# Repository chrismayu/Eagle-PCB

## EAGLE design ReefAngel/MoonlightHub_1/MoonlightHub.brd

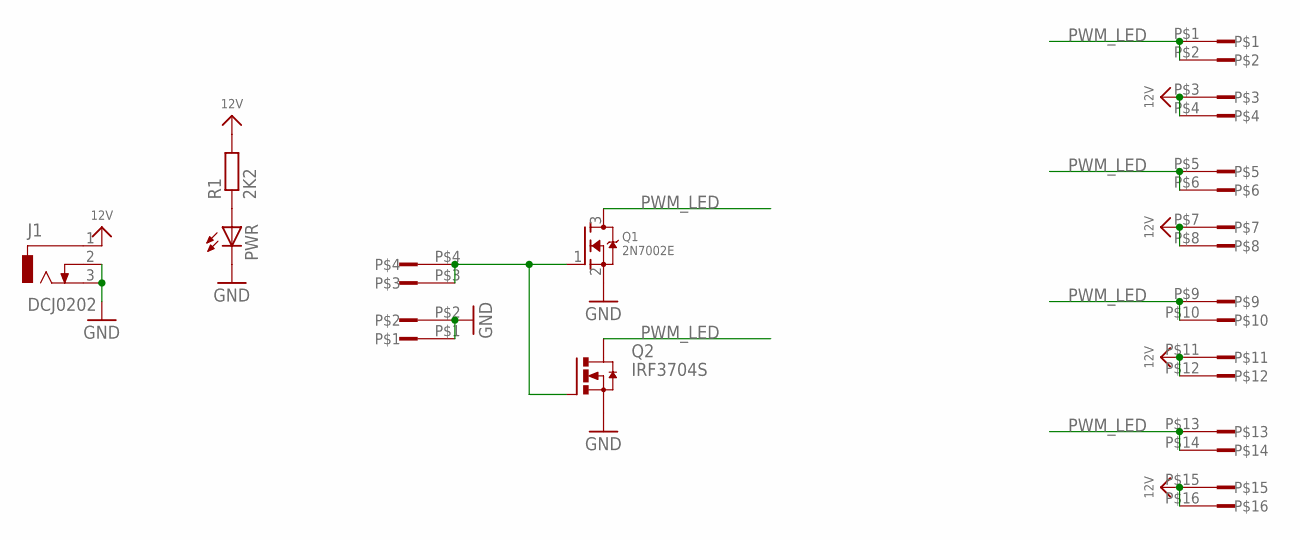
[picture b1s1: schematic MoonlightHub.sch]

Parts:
CON1: CONN2
CON2: CONN8
J1: DCJ0202
PWR: LED3MM
Q1: 2N7002E; SOT23-W
Q2: IRF3704S; D2PACK
R1: 2K2; R0805W

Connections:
12V: CON2.P$3, CON2.P$4, CON2.P$7, CON2.P$8, CON2.P$11, CON2.P$12, CON2.P$15, CON2.P$16, J1.1, R1.2
GND: CON1.P$1, CON1.P$2, J1.2, J1.3, PWR.K (C), Q1.2 (S), Q2.3 (S)
unnamed: CON1.P$3, CON1.P$4, Q1.1 (G), Q2.1 (G)
unnamed: PWR.A, R1.1
PWM_LED: CON2.P$1, CON2.P$2, CON2.P$5, CON2.P$6, CON2.P$9, CON2.P$10, CON2.P$13, CON2.P$14, Q1.3 (D), Q2.2 (D)

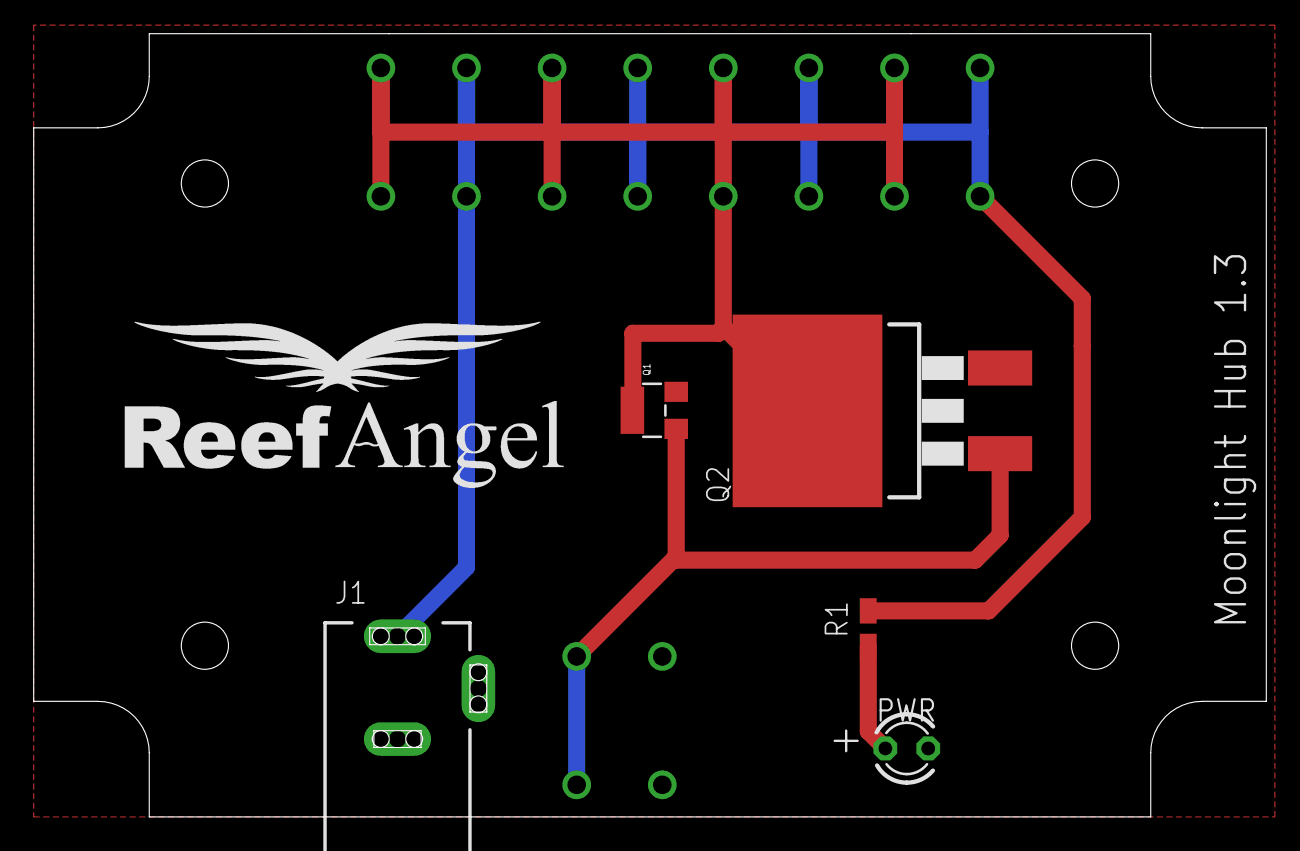
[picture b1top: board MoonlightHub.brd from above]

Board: 2 copper layers, 73.2 x 46.5 mm, 7 parts (0 on the bottom side), 5 nets.

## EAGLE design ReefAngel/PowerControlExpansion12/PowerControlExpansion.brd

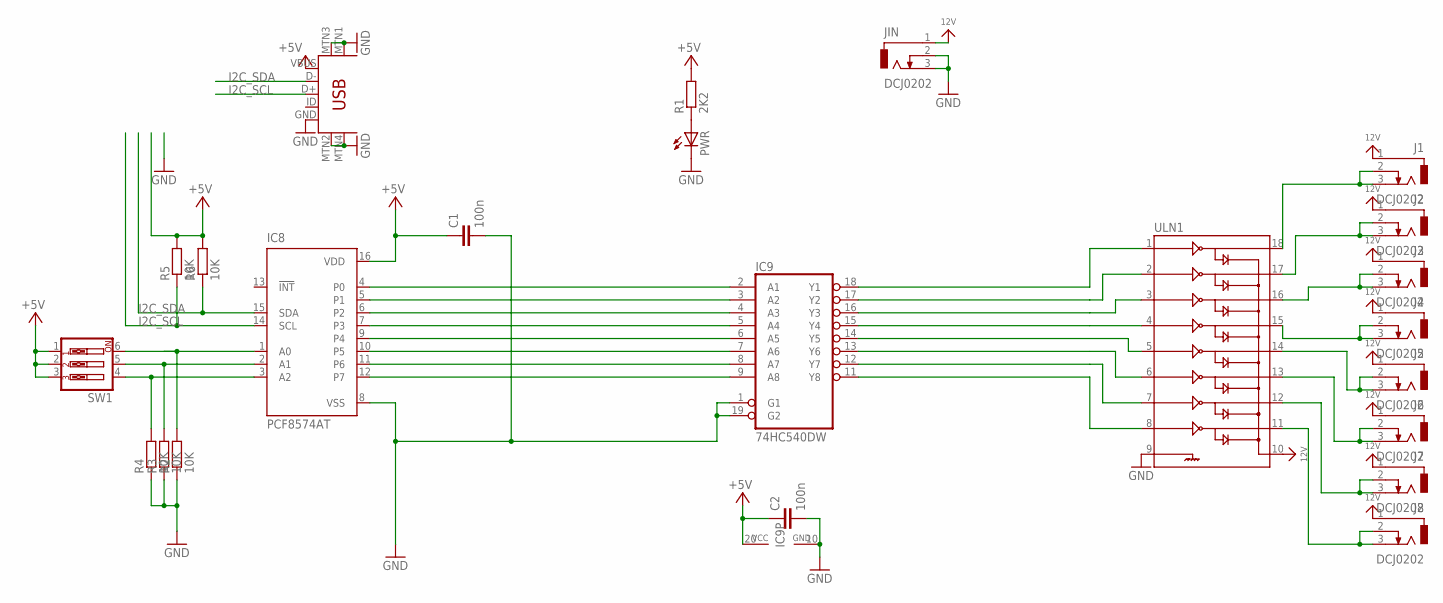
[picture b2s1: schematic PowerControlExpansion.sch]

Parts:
C1, C2: 100n; C0805K
IC8: PCF8574AT; SO16W
IC9: 74HC540DW; SO20W
J1, J2, J3, J4, J5, J6, J7, J8: DCJ0202
JIN: DCJ0202
PWR: LED3MM
R1: 2K2; R0805W
R2, R3, R4, R5, R6: 10K; R0805W
SW1: SW_DIP-3; EDG-03
U1: USB-MINIB-5PIN; USB-MINIB
ULN1: ULN2803SOICW; SO18L

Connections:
12V: J1.1, J2.1, J3.1, J4.1, J5.1, J6.1, J7.1, J8.1, JIN.1, ULN1.10
+5V: C1.1, C2.1, IC8.16 (VDD), IC9.20 (VCC), R1.2, R5.2, R6.2, SW1.1, SW1.2, SW1.3, U1.VBUS
GND: C1.2, C2.2, IC8.8 (VSS), IC9.1 (G1), IC9.10 (GND), IC9.19 (G2), JIN.2, JIN.3, PWR.K (C), R2.1, R3.1, R4.1, U1.GND, U1.MTN1 (MTN2), U1.MTN2 (MTN3), U1.MTN3 (MTN1), U1.MTN4, ULN1.9
I2C_SCL: IC8.14 (SCL), R5.1, U1.D+
I2C_SDA: IC8.15 (SDA), R6.1, U1.D-
unnamed: J1.2, J1.3, ULN1.18
unnamed: J2.2, J2.3, ULN1.17
unnamed: J3.2, J3.3, ULN1.16
unnamed: PWR.A, R1.1
unnamed: J4.2, J4.3, ULN1.15
unnamed: IC9.18 (Y1), ULN1.1
unnamed: J5.2, J5.3, ULN1.14
unnamed: J6.2, J6.3, ULN1.13
unnamed: IC8.2 (A1), R3.2, SW1.5
unnamed: IC8.3 (A2), R4.2, SW1.4
unnamed: IC8.1 (A0), R2.2, SW1.6
unnamed: IC9.17 (Y2), ULN1.2
unnamed: J7.2, J7.3, ULN1.12
unnamed: IC9.16 (Y3), ULN1.3
unnamed: J8.2, J8.3, ULN1.11
unnamed: IC9.15 (Y4), ULN1.4
unnamed: IC9.14 (Y5), ULN1.5
unnamed: IC9.13 (Y6), ULN1.6
unnamed: IC9.12 (Y7), ULN1.7
unnamed: IC9.11 (Y8), ULN1.8
unnamed: IC8.4 (P0), IC9.2 (A1)
unnamed: IC8.5 (P1), IC9.3 (A2)
unnamed: IC8.6 (P2), IC9.4 (A3)
unnamed: IC8.7 (P3), IC9.5 (A4)
unnamed: IC8.9 (P4), IC9.6 (A5)
unnamed: IC8.10 (P5), IC9.7 (A6)
unnamed: IC8.11 (P6), IC9.8 (A7)
unnamed: IC8.12 (P7), IC9.9 (A8)

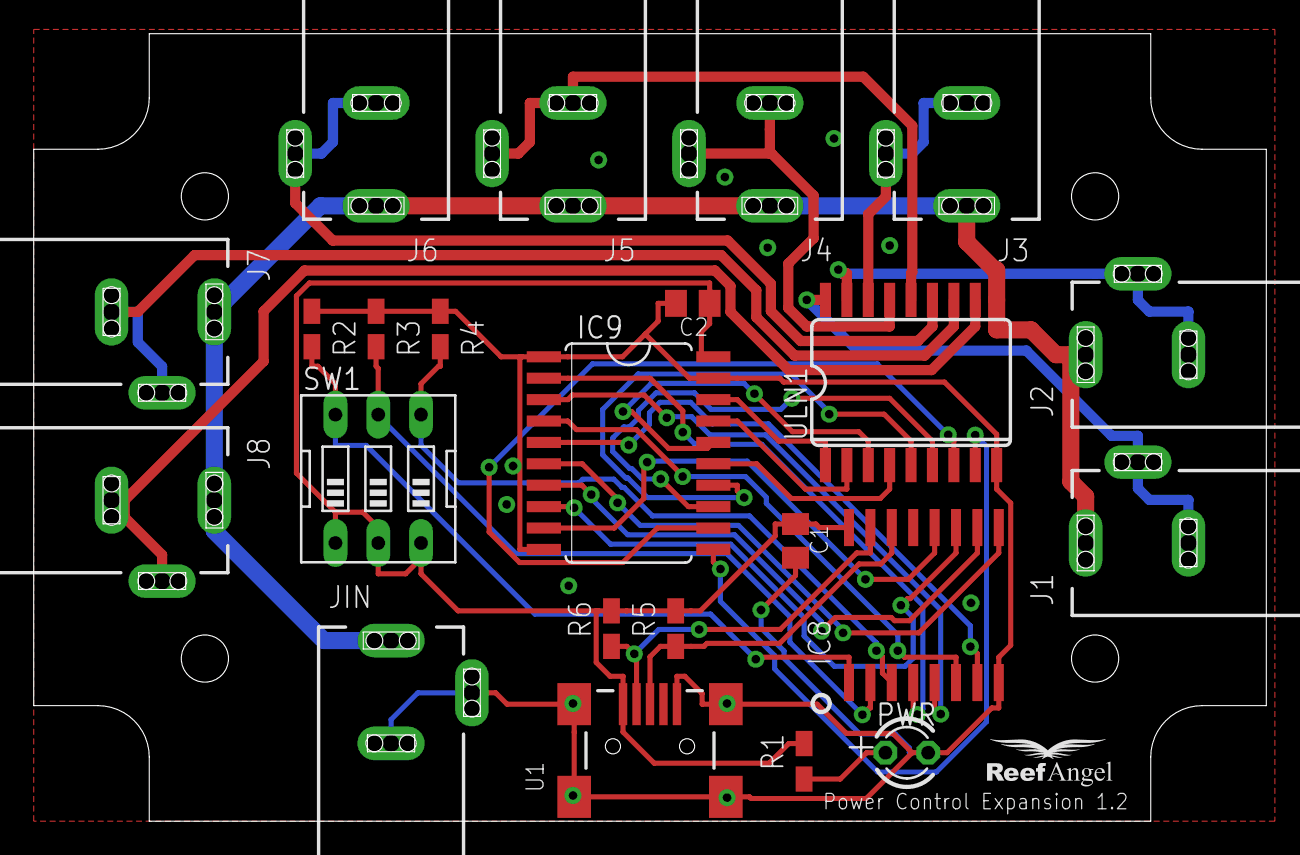
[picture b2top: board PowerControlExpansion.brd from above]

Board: 2 copper layers, 73.2 x 46.7 mm, 23 parts (0 on the bottom side), 33 nets.

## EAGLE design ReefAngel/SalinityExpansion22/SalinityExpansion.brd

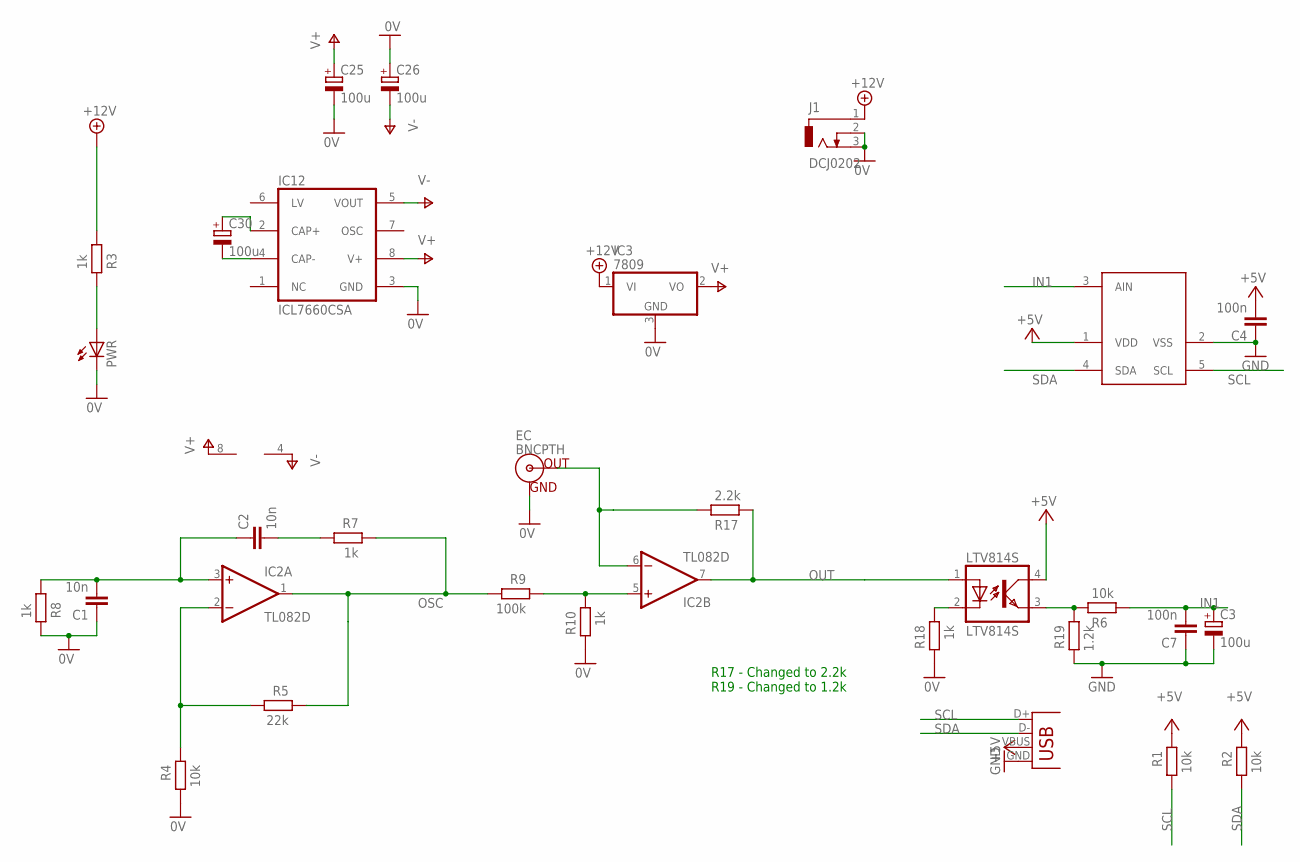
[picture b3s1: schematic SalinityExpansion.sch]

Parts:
C1, C2: 10n; C0805K
C3, C25, C26, C30: 100u; PANASONIC_D
C4, C7: 100n; C0805K
EC: BNCPTH; BNC
IC2: TL082D; SO08
IC3: 7809; TO252
IC12: ICL7660CSA; SO08
J1: DCJ0202
LTV814S: LTV814S; SMD4
PWR: LED3MM
R1, R2, R4, R6: 10k; R0805
R3, R7, R8, R10, R18: 1k; R0805
R5: 22k; R0805
R9: 100k; R0805
R17: 2.2k; R0805
R19: 1.2k; R0805
U$2: MCP3221; SOT23-5
X5: USBSMD; USB-MINIB

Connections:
0V: C1.1, C25.-, C26.+, EC.GND, IC3.3 (GND), IC12.3 (GND), J1.2, J1.3, PWR.K (C), R4.1, R8.2, R10.1, R18.1
+5V: C4.2, LTV814S.4 (COL), R1.2, R2.2, U$2.1 (VDD), X5.VBUS
+12V: IC3.1 (VI), J1.1, R3.1
GND: C3.-, C4.1, C7.1, R19.1, U$2.2 (VSS), X5.GND
IN1: C3.+, C7.2, R6.1, U$2.3 (AIN)
unnamed: LTV814S.3 (EMIT), R6.2, R19.2
unnamed: IC2.2 (-IN), R4.2, R5.1
unnamed: IC2.5 (+IN), R9.2, R10.2
unnamed: C2.2, R7.1
unnamed: PWR.A, R3.2
unnamed: EC.S (OUT), IC2.6 (-IN), R17.2
unnamed: C1.2, C2.1, IC2.3 (+IN), R8.1
unnamed: LTV814S.2 (C), R18.2
unnamed: C30.-, IC12.4 (CAP-)
unnamed: C30.+, IC12.2 (CAP+)
OSC: IC2.1 (OUT), R5.2, R7.2, R9.1
OUT: IC2.7 (OUT), LTV814S.1 (A), R17.1
SCL: R1.1, U$2.5 (SCL), X5.D+
SDA: R2.1, U$2.4 (SDA), X5.D-
V+: C25.+, IC2.8 (V+), IC3.2 (VO), IC12.8 (V+)
V-: C26.-, IC2.4 (V-), IC12.5 (VOUT)

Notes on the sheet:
R17 - Changed to 2.2k R19 - Changed to 1.2k

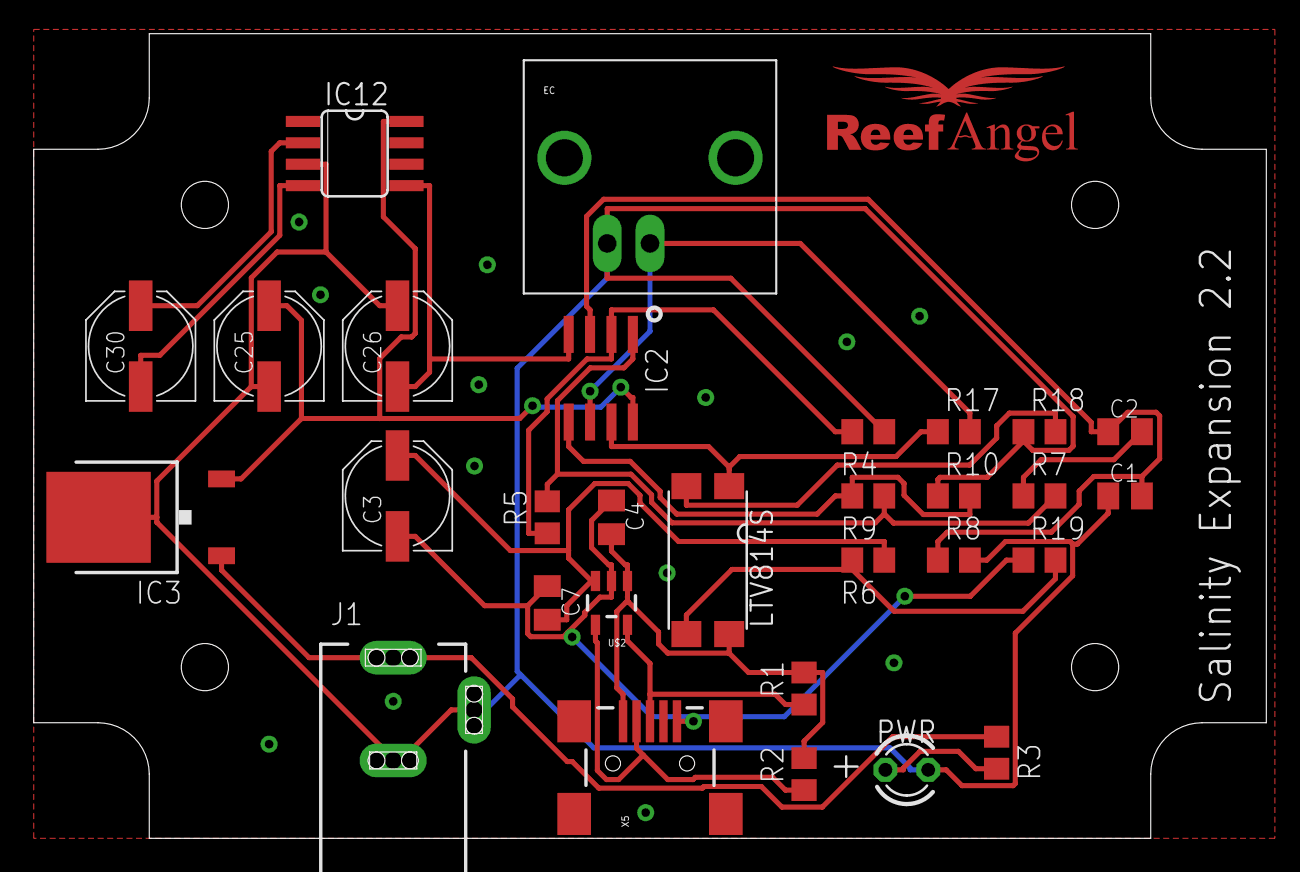
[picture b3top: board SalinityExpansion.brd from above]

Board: 2 copper layers, 73.2 x 47.8 mm, 30 parts (0 on the bottom side), 21 nets.

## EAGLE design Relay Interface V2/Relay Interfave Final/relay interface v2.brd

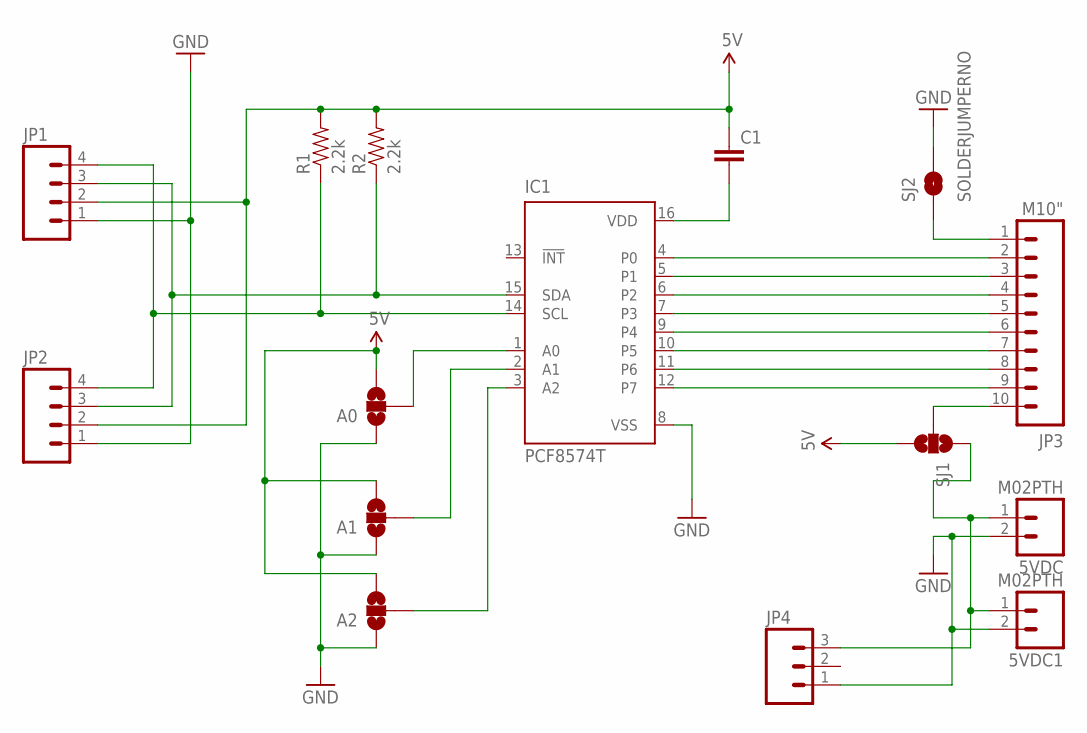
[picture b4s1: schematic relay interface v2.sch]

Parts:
5VDC, 5VDC1: M02PTH; 1X02
A0, A1, A2: SOLDERJUMPER_2WAYS; SJ_3
C1: CAPPTH2; CAP-PTH-SMALL2
IC1: PCF8574T; SO16W
JP1, JP2: M04PTH; 1X04
JP3: M10"; 1X10
JP4: M03PTH; 1X03
R1, R2: 2.2k; 1206
SJ1: SOLDERJUMPER_2WAYS; SJ_3
SJ2: SOLDERJUMPERNO; SJ_2S-NO

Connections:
5V: A0.3, A1.3, A2.3, C1.1, JP1.2, JP2.2, R1.2, R2.2, SJ1.3
GND: 5VDC.2, 5VDC1.2, A0.1, A1.1, A2.1, IC1.8 (VSS), JP1.1, JP2.1, JP4.1, SJ2.2
unnamed: IC1.4 (P0), JP3.2
unnamed: IC1.5 (P1), JP3.3
unnamed: IC1.6 (P2), JP3.4
unnamed: A0.2, IC1.1 (A0)
unnamed: IC1.14 (SCL), JP1.4, JP2.4, R1.1
unnamed: IC1.15 (SDA), JP1.3, JP2.3, R2.1
unnamed: A1.2, IC1.2 (A1)
unnamed: C1.2, IC1.16 (VDD)
unnamed: A2.2, IC1.3 (A2)
unnamed: IC1.7 (P3), JP3.5
unnamed: IC1.9 (P4), JP3.6
unnamed: IC1.10 (P5), JP3.7
unnamed: IC1.11 (P6), JP3.8
unnamed: IC1.12 (P7), JP3.9
unnamed: 5VDC.1, 5VDC1.1, JP4.3, SJ1.1
unnamed: JP3.1, SJ2.1
unnamed: JP3.10, SJ1.2

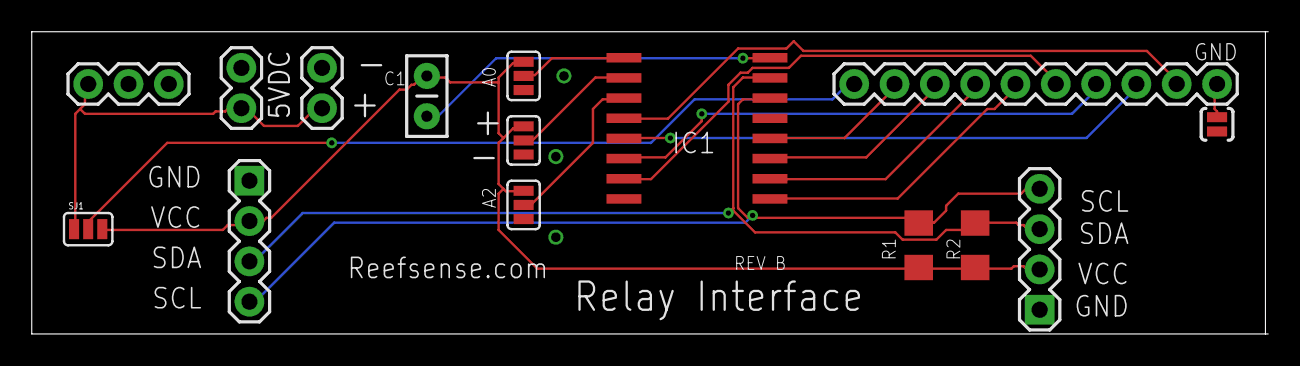
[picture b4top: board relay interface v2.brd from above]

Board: 2 copper layers, 77.7 x 19.0 mm, 15 parts (0 on the bottom side), 19 nets.

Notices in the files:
parts and their libraries:
microbuilder: This work is placed in the public domain, and may be freely used for commercial and non-commercial work with the following conditions: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
SparkFun-Capacitors: Licensing: Creative Commons ShareAlike 4.0 International - https://creativecommons.org/licenses/by-sa/4.0
